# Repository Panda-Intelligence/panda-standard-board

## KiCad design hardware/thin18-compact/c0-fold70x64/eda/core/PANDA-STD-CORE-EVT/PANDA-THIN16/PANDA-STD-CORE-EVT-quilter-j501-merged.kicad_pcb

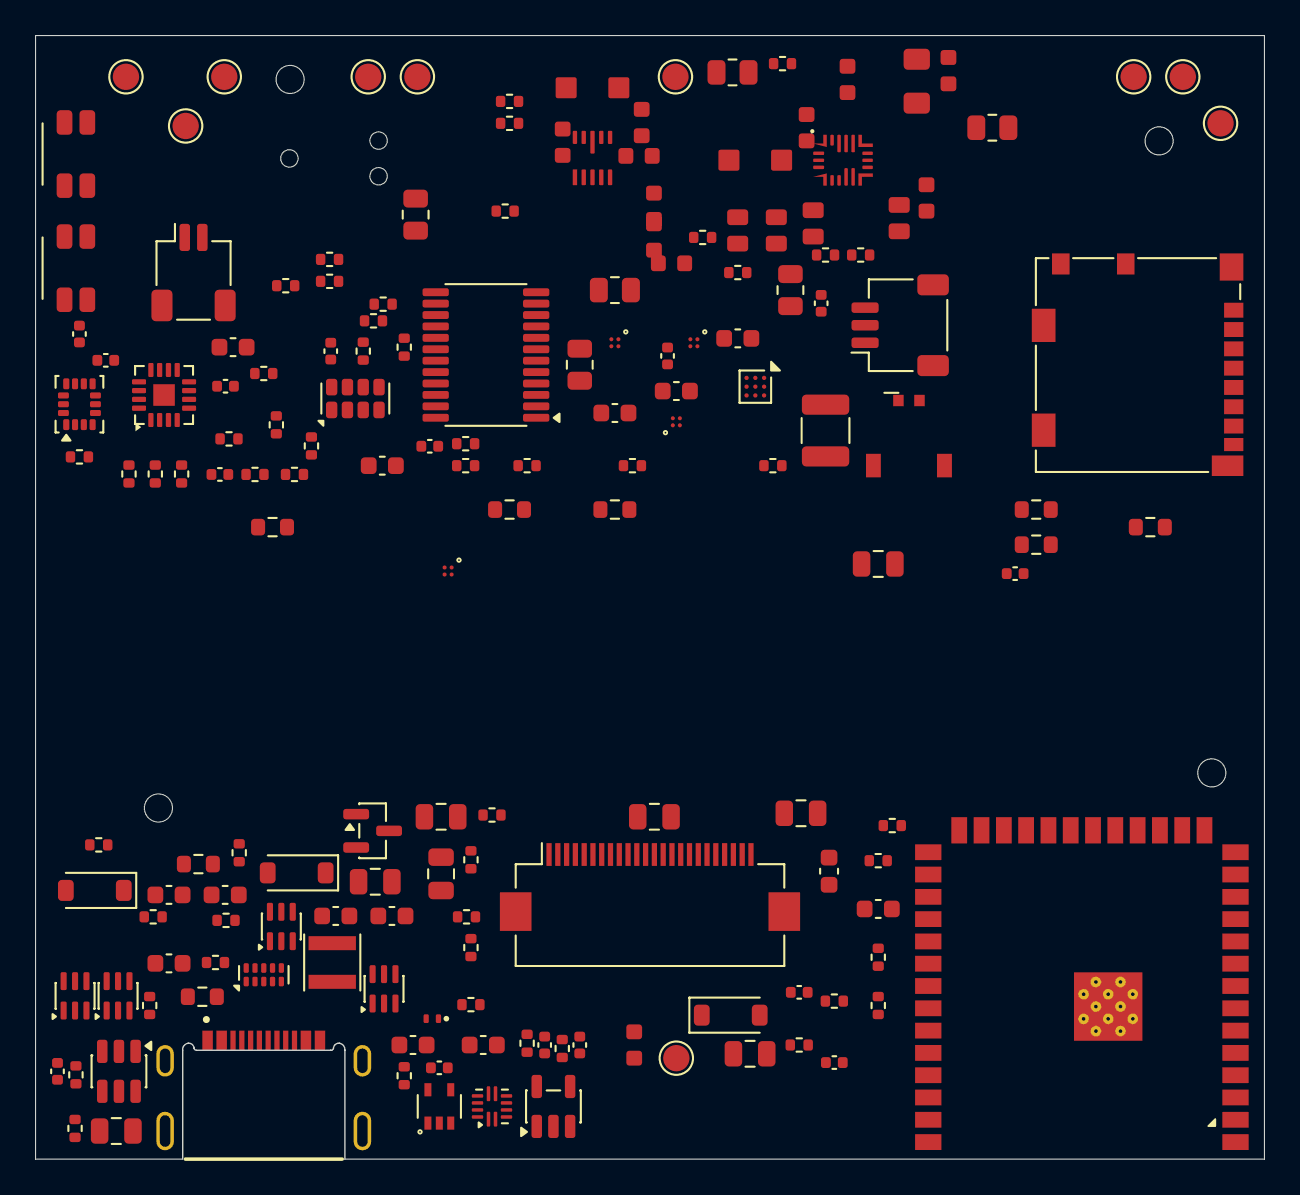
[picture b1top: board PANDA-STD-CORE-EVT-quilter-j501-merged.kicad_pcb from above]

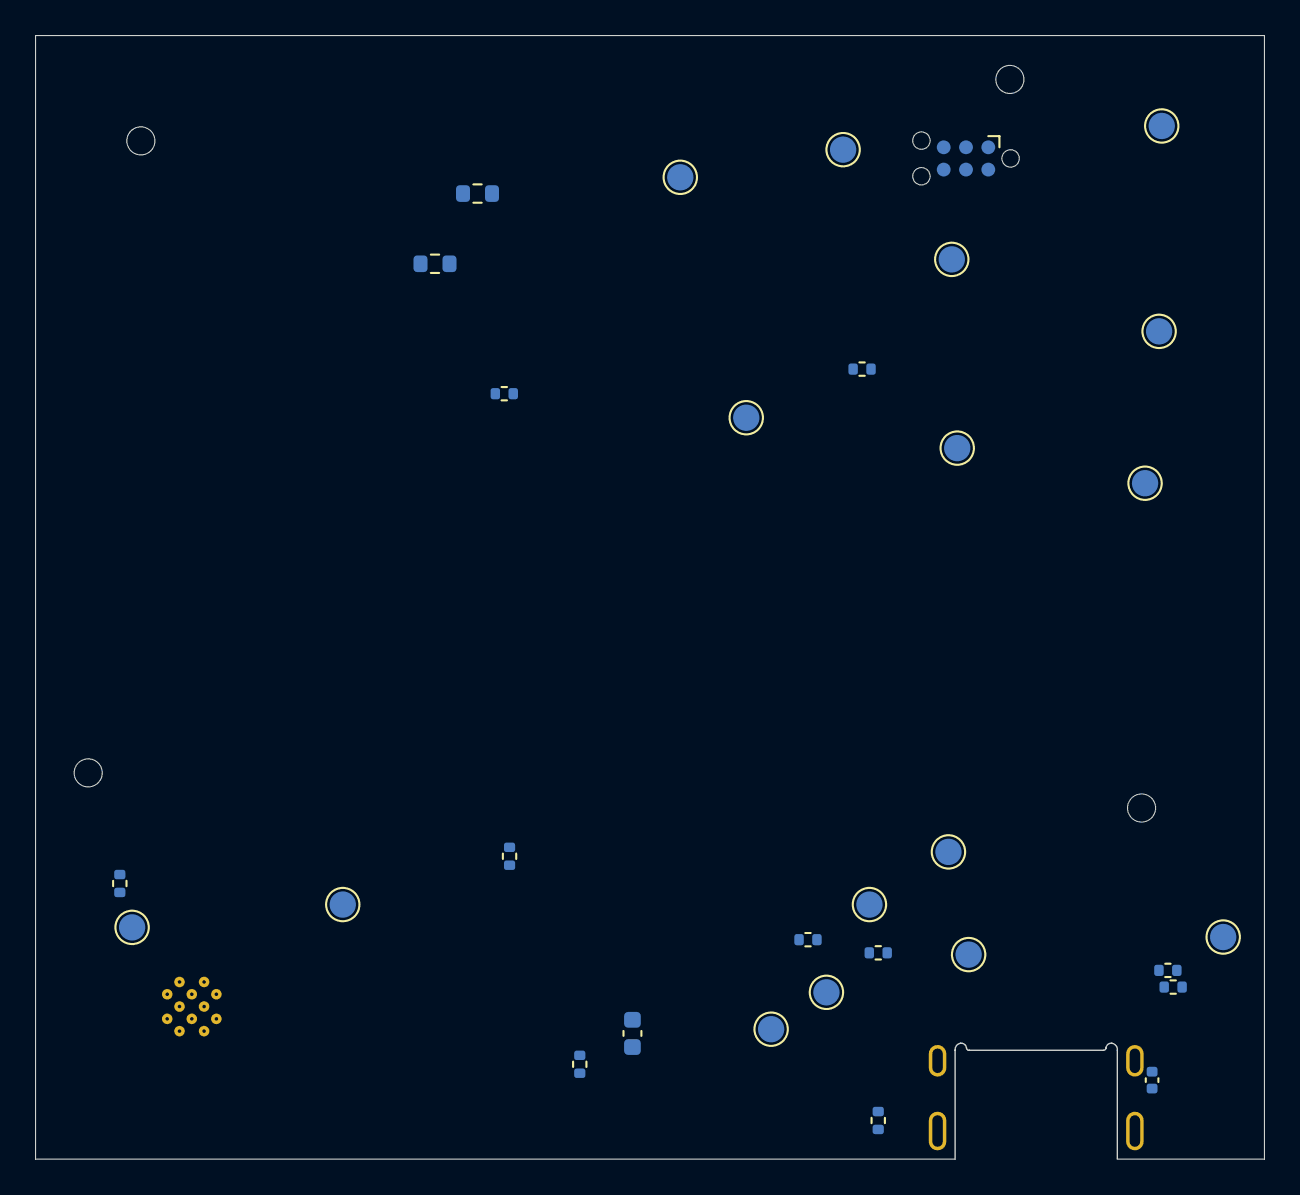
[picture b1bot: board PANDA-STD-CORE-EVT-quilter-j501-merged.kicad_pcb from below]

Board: 4 copper layers, 70.0 x 64.0 mm, 202 parts (31 on the bottom side), 124 nets, no tracks yet.

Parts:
C201: 47n / CBOOT; C201_CBOOT_0603_SEED
C202: 1u / VBUS; C202_CVBUS_0603_ENVELOPE
C203: 10u / PMID; C203_CPMID_1206_ENVELOPE
C204: 330n / ILIM-RC; C204_ILIM_RC_0603_SEED
C205: 4.7u / REGN; C205_CREGN_0805_ENVELOPE
C206: 10u / BAT; C206_CBAT_0805_ENVELOPE
C207: 22u / CSYS1; C207_CSYS_0805_ENVELOPE
C208: 22u / CSYS2; C208_CSYS_0805_ENVELOPE
C209: 1u; C_0603_1608Metric
C210: 2.2u; C_0603_1608Metric
C211, C212, C213, C214: 100n; C_0402_1005Metric
C215: 1n; C_0402_1005Metric
C301: CPH3225A 11mF 3.3V RTC backup candidate; C_1210_3225Metric
C302: 100n / RTC VDD; C_0402_1005Metric
C303: 1u / BQ BAT; C_0402_1005Metric
C304: 2.2u / BQ VDD; C_0402_1005Metric
C401: 22u / VIN; C_0603_POWER_SEED
C402, C403: 22u / VOUT; C_0603_POWER_SEED
C501: 22u / ESP32; C_0805_2012Metric
C502: 100n / ESP32; C_0402_1005Metric
C503: 100n / VDD_IO; C_0402_1005Metric
C504: 100n / VDD; C_0402_1005Metric
C505: 100n / AUDIO_VDD; C_0402_1005Metric
C506: 10u / AUDIO_VDD; C_0603_1608Metric
C507: 1u / U405 VIN; C_0603_1608Metric
C508: 1u / U402 VIN; C_0603_1608Metric
C509: 1u / U403 VIN; C_0603_1608Metric
C510: 1u / CHIP_PU; C_0603_1608Metric
C511: 1u / U404 VIN; C_0603_1608Metric
C512: 100n / SD VDD; C_0402_1005Metric
C513: 10u / SD VDD; C_0603_1608Metric
C514, C515: DNP / USB tuning; C_0402_1005Metric
C601: 100n / U601 VCC; C_0402_1005Metric
C801, C802, C803: 1u 25V X5R; C_0603_1608Metric
C804, C805, C806, C807, C808, C809: 4.7u 25V X5R; C_0805_2012Metric
C810: 1u 25V X7R; C_0805_2012Metric
C811, C812, C813: 100n 25V X7R; C_0603_1608Metric
D201: TPD4E05U06DQAR; USON-10_2.5x1.0mm_P0.5mm
D202: TPD1E10B06DPYR; Texas_DPY0002A_0.6x1mm_P0.65mm
D801, D802, D803: MBR0530T1G; D_SOD-123
H801, H802, H803, H804: M1.2 clearance / NPTH 1.6; MountingHole_M1.2_1.6mm
J201: USB4500-03-0-A; USB4500_08mm_MidMount_LayoutReview
J301: DF58-2P-1.2V(21); Hirose_DF58-2P-1.2V_1x02_P1.2mm_Vertical
J302: SM03B-SRSS-TB NTC; JST_SH_SM03B-SRSS-TB_1x03-1MP_P1.00mm_Horizontal
J501: 104031-0811 / microSD; microSD_HC_Molex_104031-0811
J502: SM02B-SRSS-TB; JST_SH_SM02B-SRSS-TB_1x02-1MP_P1.00mm_Horizontal
J503: TC2030-IDC-NL / DEBUG; Tag-Connect_TC2030-IDC-NL_2x03_P1.27mm_Vertical
J802: FH12-24S-0.5SH(55); Hirose_FH12-24S-0.5SH_1x24-1MP_P0.50mm_Horizontal
L401: 0.47uH / M0-PENDING; L401_XFL4015_ENVELOPE
L402: 2.2u / BQ buck; L402_2U2_ENVELOPE
L801: 47u 0.25A; L_Taiyo_NRH3010_3030
Q801: NX3008NBK,215; SOT-23
R201: 5.6k / ILIM; R201_ILIM_0603_SEED
R204: 1.2k / ILIM-RC; R204_ILIM_RC_0603_SEED
R205: 887k; R_0402_1005Metric
R206, R207: 4.7k; R_0402_1005Metric
R208: 47k; R_0402_1005Metric
R209: 1k; R_0603_1608Metric
R210: 105k; R_0402_1005Metric
R211, R212, R528, R602, R603, R814: 10k; R_0402_1005Metric
R213, R214, R807, R808, R809, R810, R811, R812: 100k; R_0402_1005Metric
R301: 1M / SCL PD DNP; R_0402_1005Metric
R302: 1M / SDA PD DNP; R_0402_1005Metric
R303: 10k / RTC EVI PU; R_0402_1005Metric
R304: 10k / VBACKUP no-backup / DNP with C301; R_0402_1005Metric
R305: 100k / IRQ PU DNP; R_0402_1005Metric
R306: 0R / MB1 BAT; R_0805_2012Metric
R307: 10k / BIN PD; R_0402_1005Metric
R401: 560k; R_0603_FEEDBACK_SEED
R402: 100k; R_0603_FEEDBACK_SEED
R403: 100k / PG; R_0603_FEEDBACK_SEED
R501: 100k / IMU_INT1; R_0402_1005Metric
R502: 100k / EXP_INT_PU; R_0402_1005Metric
R503: 10k / SD_MODE; R_0402_1005Metric
R504: 0R / GAIN 12dB; R_0402_1005Metric
R505: 100k / GAIN 15dB DNP; R_0402_1005Metric
R506: 0R / GAIN 6dB DNP; R_0402_1005Metric
R507: 100k / AUDIO_EN_PD; R_0402_1005Metric
R508: 0R / MB6 AUDIO; R_0805_2012Metric
R509: 0R / MB2 3V3_AON; R_0805_2012Metric
R510: 10k / CHIP_PU; R_0402_1005Metric
R511: 10k / GPIO0; R_0402_1005Metric
R512: 10k / GPIO3; R_0402_1005Metric
R513: 10k / GPIO46; R_0402_1005Metric
R514: 0R / MB3 SD; R_0805_2012Metric
R515: 0R / MB4 TOUCH; R_0805_2012Metric
R516: 0R / MB5 EPD; R_0805_2012Metric
R517, R518, R519, R520, R521, R522: 0R / SD series; R_0603_1608Metric
R523, R524, R525, R526, R527: 10k / SD pull-up; R_0402_1005Metric
R529, R530, R801, R802, R803, R804, R805: 22; R_0402_1005Metric
R600: 10k 1% / PG_PU; R_0402_1005Metric
R601: 100k / P15_PD; R_0402_1005Metric
R604: 100k / SD_EN_PD; R_0402_1005Metric
R605: 100k / TOUCH_EN_PD; R_0402_1005Metric
R606: 100k / EPD_EN_PD; R_0402_1005Metric
R607: 100k / BQ_CE_PD; R_0402_1005Metric
R608: 100k / FUEL_PU; R_0402_1005Metric
R609: 100k / BQ_INT_PU; R_0402_1005Metric
R610: 100k / BQ_STAT_PU; R_0402_1005Metric
R611: 100k / KEY_FN_PU; R_0402_1005Metric
R612: 100k / SD_CD_PU; R_0402_1005Metric
R613: 2.2k / I2C_SCL_PU A; R_0402_1005Metric
R614: 2.2k / I2C_SDA_PU A; R_0402_1005Metric
R615: 5.23k; R_0603_1608Metric
R616: 30.1k; R_0603_1608Metric
R806: 100; R_0402_1005Metric
R813: 2.2 1%; R_0603_1608Metric
SW201, SW202: SKSCLCE010; SW_Alps_SKSCLCE010
TP1: VBUS_USB; TestPoint_Pad_D1.5mm
TP2: VSYS_RAW; TestPoint_Pad_D1.5mm
TP3: 3V3_AON; TestPoint_Pad_D1.5mm
TP4: BAT+; TestPoint_Pad_D1.5mm
TP5: 3V3_SD; TestPoint_Pad_D1.5mm
TP6: 3V3_TOUCH; TestPoint_Pad_D1.5mm
TP7: 3V3_EPD_LOGIC; TestPoint_Pad_D1.5mm
TP8: VSYS_AUDIO; TestPoint_Pad_D1.5mm
TP11: I2C_SCL; TestPoint_Pad_D1.5mm
TP12: I2C_SDA; TestPoint_Pad_D1.5mm
TP13: EXP_INT; TestPoint_Pad_D1.5mm
TP14: EXP_INT / SHARED_IRQ; TestPoint_Pad_D1.5mm
TP16: PG_3V3_MAIN; TestPoint_Pad_D1.5mm
TP18: CHIP_PU; TestPoint_Pad_D1.5mm
TP801: Reserved EPD_D6; TestPoint_Pad_D1.5mm
TP802: Reserved EPD_D7; TestPoint_Pad_D1.5mm
TP803: Reserved EPD_CKH; TestPoint_Pad_D1.5mm
TP804: Reserved EPD_STV; TestPoint_Pad_D1.5mm
TP805: Reserved EPD_CKV; TestPoint_Pad_D1.5mm
TP806: Reserved EPD_STH; TestPoint_Pad_D1.5mm
TPG1, TPG2, TPG3, TPG4, TPG5, TPG6: GND; TestPoint_Pad_D1.5mm
U201: BQ25628ERYKR; BQ25628ERYKR_RYK0018A
U202: TUSB320LIRWBR; Texas_X2QFN-12_1.6x1.6mm_P0.4mm
U203: TPS70933DBVR; SOT-23-5
U204: SN74AUP2G07DCKR; SOT-363_SC-70-6
U205: TPS3700DDCR; TSOT-23-6
U206: 74LVC1G17XC5G/TR; SGM74LVC1G17_SC70_5_RevA
U301: BQ27427YZFR; Texas_DSBGA-9_1.62x1.58mm_Layout3x3_P0.5mm
U302: RV-3028-C7; MicroCrystal_C7_SON-8_1.5x3.2mm_P0.9mm
U401: TPS63802DLA
U402, U403, U404, U405: TPS22916CYFPT; TPS22916CYFPT_YFP0004
U501: ESP32-S3-WROOM-1U-N16R8; ESP32-S3-WROOM-1U
U502: MAX98357AETE+T; MAX98357AETE_T_TQFN16
U503: LSM6DSO32XTR; LGA-14_3x2.5mm_P0.5mm_LayoutBorder3x4y
U601: TCA9535PWR; TCA9535PWR_PW0024A
U801, U802, U803: SN74AUP2G17DCKR; SOT-363_SC-70-6

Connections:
3V3_AON: C214.1, C302.1, C501.1, C502.1, C503.1, C504.1, C508.1, C509.1, C511.1, C601.1, J503.2, R303.1, R305.1, R502.2, R509.2, R510.1, R511.1, R528.1, R600.2, R602.2, R603.2, R608.2, R609.2, R610.2, R611.2, R612.2, R613.2, R614.2, TP3.1, U206.5, U302.7, U402.A2, U403.A2, U404.A2, U501.2, U503.1, U503.5, U503.8, U503.12, U601.24
3V3_AON_SRC: C402.1, C403.1, R401.1, R403.1, R509.1, U401.6
3V3_EPD_LOGIC: C801.1, C802.1, C811.1, C812.1, C813.1, J802.15, J802.16, L801.1, R516.2, R809.2, TP7.1, U801.5 (VCC), U802.5 (VCC), U803.5 (VCC)
3V3_EPD_LOGIC_SW: R516.1, U404.A1
3V3_SD: C512.1, C513.1, J501.4, R514.2, R523.2, R524.2, R525.2, R526.2, R527.2, TP5.1
3V3_SD_SW: R514.1, U402.A1
3V3_TOUCH: R515.2, TP6.1
3V3_TOUCH_SW: R515.1, U403.A1
3V3_USB_CC: C210.1, C211.1, C212.1, C213.1, R206.1, R207.1, R208.1, R212.1, U202.12, U203.5, U204.5, U205.5
BAT_CONN_P: J301.1, R306.1, TP4.1
BAT_PACKP: C303.1, R306.2, U301.C3
BQ_BTST: C201.1, U201.1
BQ_CE: R607.1, U201.14, U601.9
BQ_ILIM: R201.1, R204.1, U201.4
BQ_ILIM_RC: C204.1, R204.2
BQ_INT: R609.1, U201.11, U601.10
BQ_PG: R600.1, U201.3, U601.13
BQ_PMID: C203.1, U201.17
BQ_QON: SW202.1, U201.7
BQ_REGN: C205.1, U201.2
BQ_STAT: R610.1, U201.10, U601.11
BQ_SW: C201.2, L402.1, U201.16
BQ_TS: J302.1, R615.2, R616.1, U201.6
BQ_TS_BIAS: R615.1, U201.5
CC_OUT1_AON: R602.1, U204.6, U601.19
CC_OUT1_LOCAL: R206.2, U202.7, U204.1
CC_OUT2_AON: R603.1, U204.4, U601.20
CC_OUT2_LOCAL: R207.2, U202.8, U204.3
CHIP_PU: C510.1, J503.1, R510.2, TP18.1, U501.3
EN_3V3_EPD_LOGIC: R606.1, U404.B2, U601.6
EN_3V3_SD: R604.1, U402.B2, U601.4
EN_3V3_TOUCH: R605.1, U403.B2, U601.5
EN_VSYS_AUDIO: R507.1, U405.B2, U601.7
EPD16_BOOST_CP: C804.2, D801.1 (K), D802.2 (A)
EPD16_BOOST_SW: C804.1, D803.2 (A), L801.2, Q801.3 (D)
EPD16_BUF_CS: R803.1, U802.6 (1Y)
EPD16_BUF_DC: R804.1, U802.4 (2Y)
EPD16_BUF_MOSI: R802.1, U801.4 (2Y)
EPD16_BUF_RESET: R805.1, U803.6 (1Y)
EPD16_BUF_SCLK: R801.1, U801.6 (1Y)
EPD16_BUSY: J802.9, R806.1
EPD16_CS: J802.12, R803.2
EPD16_DC: J802.11, R804.2
EPD16_GDR: J802.2, Q801.1 (G), R814.1
EPD16_MOSI: J802.14, R802.2
EPD16_RESE: J802.3, Q801.2 (S), R813.1
EPD16_RESET: J802.10, R805.2
EPD16_SCLK: J802.13, R801.2
EPD16_VCOM: C810.1, J802.24
EPD16_VDD1V5: C803.1, J802.18
EPD16_VGH: C806.1, D803.1 (K), J802.21
EPD16_VGL: C805.1, D801.2 (A), J802.23
EPD16_VSH1: C808.1, J802.20
EPD16_VSH2: C807.1, J802.5
EPD16_VSL: C809.1, J802.22
EPD_CKH: TP803.1, U501.9
EPD_CKV: TP805.1, U501.11
EPD_D0: R807.1, U501.31, U801.1 (1A)
EPD_D1: R808.1, U501.32, U801.3 (2A)
EPD_D2: R809.1, U501.33, U802.1 (1A)
EPD_D3: R810.1, U501.34, U802.3 (2A)
EPD_D4: R811.1, U501.35, U803.1 (1A)
EPD_D5: R806.2, R812.1, U501.24
EPD_D6: TP801.1, U501.25
EPD_D7: TP802.1, U501.23
EPD_LE: R512.1, U501.15
EPD_OE: R513.1, U501.16
EPD_STH: TP806.1, U501.26
EPD_STV: TP804.1, U501.10
EXP_INT: R305.2, R502.1, TP13.1, TP14.1, U302.2, U501.4, U601.1
EXP_P15_SPARE: R601.1, U601.18
FB_3V3: R401.2, R402.1, U401.4
FUEL_BIN: R307.1, U301.B1
FUEL_GPOUT: R608.1, U301.A1, U601.8
FUEL_VDD: C304.1, U301.B3
GAIN_SLOT: R504.1, R505.1, R506.1, U502.2
GND: C202.2, C203.2, C204.2, C205.2, C206.2, C207.2, C208.2, C209.2, C210.2, C211.2, C212.2, C213.2, C214.2, C215.2, C301.2, C302.2, C303.2, C304.2, C401.2, C402.2, C403.2, C501.2, C502.2, C503.2, C504.2, C505.2, C506.2, C507.2, C508.2, C509.2, C510.2, C511.2, C512.2, C513.2, C514.2, C515.2, C601.2, C801.2, C802.2, C803.2, C805.2, C806.2, C807.2, C808.2, C809.2, C810.2, C811.2, C812.2, C813.2, D201.3, D201.8, D202.2, D802.1 (K), J201.A1, J201.A12, J201.B1, J201.B12, J201.SH, J301.2, J302.2, J501.6, J501.10, J501.SH, J503.4, J802.6, J802.7, J802.8, J802.17, R201.2, R208.2, R209.2, R211.2, R213.2, R214.2, R301.2, R302.2, R304.2, R307.2, R402.2, R501.2, R504.2, R505.2, R507.2, R512.2, R513.2, R601.2, R604.2, R605.2, R606.2, R607.2, R616.2, R807.2, R808.2, R810.2, R811.2, R812.2, R813.2, R814.2, SW201.2, SW202.2, TPG1.1, TPG2.1, TPG3.1, TPG4.1, TPG5.1, TPG6.1, U201.15, U202.3, U202.10, U202.11, U203.2, U204.2, U205.2, U205.4, U206.3, U301.B2, U301.C1, U302.5, U401.2, U401.3, U401.8, U402.B1, U403.B1, U404.B1, U405.B1, U501.1, U501.40, U501.41, U502.3, U502.11, U502.15, U502.17, U503.2, U503.3, U503.6, U503.7, U601.2, U601.3, U601.12, U601.21, U801.2 (GND), U802.2 (GND), U803.2 (GND), U803.3 (2A)
GPIO0: J503.6, R511.2, U501.27
I2C_SCL: R301.1, R613.1, TP11.1, U201.13, U301.A3, U302.3, U501.22, U503.13, U601.22
I2C_SDA: R302.1, R614.1, TP12.1, U201.12, U301.A2, U302.4, U501.8, U503.14, U601.23
I2S_BCLK: U501.19, U502.16
I2S_DIN: U501.21, U502.1
I2S_LRCLK: U501.20, U502.14
IMU_INT1: R501.1, U503.4, U601.15
KEY_FN: R611.1, U601.14
KEY_POWER_MCU: R528.2, SW201.1, U501.39
PACK_BAT: C206.1, U201.8, U301.C2
PG_3V3_MAIN: R403.2, TP16.1, U401.5, U601.17
RTC_EVI: R303.2, U302.8
RTC_VBACKUP: C301.1, R304.1, U302.6
SDMMC_CLK: R517.1, U501.5
SDMMC_CLK_CARD: J501.5, R517.2
SDMMC_CMD: R518.1, U501.6
SDMMC_CMD_CARD: J501.3, R518.2, R523.1
SDMMC_D0: R519.1, U501.7
SDMMC_D0_CARD: J501.7, R519.2, R524.1
SDMMC_D1: R520.1, U501.12
SDMMC_D1_CARD: J501.8, R520.2, R525.1
SDMMC_D2: R521.1, U501.17
SDMMC_D2_CARD: J501.1, R521.2, R526.1
SDMMC_D3: R522.1, U501.18
SDMMC_D3_CARD: J501.2, R522.2, R527.1
SD_CD: J501.9, R612.1, U601.16
SD_MODE: R503.2, U502.4
SPK_N: J502.2, U502.10
SPK_P: J502.1, U502.9
SW_L1: L401.1, U401.9
SW_L2: L401.2, U401.7
TUSB_VBUS_DET: R205.2, U202.4
UART0_RX: J503.3, U501.36
UART0_TX: J503.5, U501.37
USB_CC1: D201.4, J201.A5, U202.1
USB_CC2: D201.5, J201.B5, U202.2
USB_DM: D201.2, J201.A7, J201.B7, R530.1
USB_DM_MCU: C515.1, R530.2, U501.13
USB_DP: D201.1, J201.A6, J201.B6, R529.1
USB_DP_MCU: C514.1, R529.2, U501.14
VBUS_SENSE: C215.1, R210.2, R211.1, U205.3
VBUS_USB: C202.1, C209.1, D202.1, J201.A4, J201.A9, J201.B4, J201.B9, R205.1, R209.1, R210.1, TP1.1, U201.18, U203.1
VBUS_VALID_AON: R214.1, U206.4, U501.38
VBUS_VALID_CC: R212.2, R213.1, U205.1, U206.2
VSYS_AUDIO: C505.1, C506.1, R503.1, R506.2, R508.2, TP8.1, U502.7, U502.8
VSYS_AUDIO_SW: R508.1, U405.A1
VSYS_RAW: C207.1, C208.1, C401.1, C507.1, L402.2, TP2.1, U201.9, U401.1, U401.10, U405.A2
